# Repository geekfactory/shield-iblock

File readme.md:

# Shield iBlock

Shield para Arduino Uno R3 (y tarjetas que comparten las mismas dimensiones) que permite conectar módulos y accesorios compatibles con el sistema iBlock desarrollado por Geek Factory.

Este shield "exporta" los puertos de la tarjeta Arduino Uno a cables planos de 10 hilos que pueden usarse para interconectar con otros módulos o el protoboard.

El sistema iBlock esta diseñado para usarse durante el aprendizaje de sistemas digitales programables o para desarrollar aplicaciones finales.

## Sistema iBlock

Se trata de una solución de conectividad diseñada para facilitar la reutilización de hardware en prototipos y sistemas realizados para producción. Esta basada en el uso de conectores [IDC (Insulation Displacement Connector)](https://en.wikipedia.org/wiki/Insulation-displacement_connector) y cable plano.

Principalmente se contempla el uso de conectores de 10 pines que permoiten llevar 8 bits o pines de I/O de propósito general y además la tierra y el voltaje de alimentación.

En este sistema cada uno de los módulos se diseñan con una distribución de pines conocida, de forma que sea posible intercambiar y reutilizar el hardware según las necesidades del proyecto.

La distribución de pines en el conector IDC-10 es la siguiente:

1. D0
2. D1
3. D2
4. D3
5. D4
6. D5
7. D6
8. D7
9. GND
10. V+ (3.3 o 5 volts)

Como el arduino Uno dispone de más puertos digitales, se continua en otro conector:

1. D8
2. D9
3. D10
4. D11
5. D12
6. D13
7. NC (sin conexión)
8. NC (sin conexión)
9. GND
10. V+ (3.3 o 5 volts)

La distribución es similar para los pines analógicos de la tarjeta.

## Periféricos y características

* 3 conectores IDC-10 que exponen todos los puertos digitales y analógicos de la tarjeta arduino
	* DIGITAL1 - Expone los pines del 0 al 7 digitales
	* DIGITAL2 - Expone los pines del 8 al 13 digitales
	* ANALOG1 - Expone los pines A0 al A5 analógicos
* 20 conectores tipo servo que brindan acceso a la alimentación y a todas las señales (D0 - D13 y A0 - A5)
* Diseño apilable que permite colocar otros shields o accesorios arriba de esta placa, incluso el conector SPI (ISP) se replica a otros shields
* Se utilizan conectores IDC-10 en angulo que permite la conexión del cable plano cuando hay otro shield colocado encima
* Selección de voltaje de alimentación (3.3 volts o 5 volts) en cada uno de los conectores IDC-10 mediante interruptores
* Conector Nanobus que permite expandir la funcionalidad del shield con otros módulos desarrollados para este estándar
* Dimensiones del PCB: 76.2 mm x 53.34mm (3 x 2.1 pulgadas)

## Contenido del repositorio

1. __root__ - Archivos fuente de EAGLE para esta placa
2. __/documents__ - Documentación adicional, hojas de datos de componentes e instrucciones de ensamble
3. __/production__ - Histórico de gerbers enviados a producción
4. __/extras__ - Dibujos técnicos, imagehes, hardware de montaje adicional y diseños de accesorios relacionados
4. __/firmware__ - Si existe el firmware de prueba o definitivo de esta placa

## Licencia de uso

**Este proyecto se publica como hardware de codigo abierto. Favor de leer detenidamente el archivo license.md para información detallada de la licencia.**

**Reconocimiento-NoComercial-CompartirIgual 4.0 Internacional (CC BY-NC-SA 4.0)**

Esto es un resumen inteligible para humanos (y no un sustituto) de la licencia.

Usted es libre de:

* __Compartir__ — copiar y redistribuir el material en cualquier medio o formato
* __Adaptar__ — remezclar, transformar y crear a partir del material

El licenciador no puede revocar estas libertades mientras cumpla con los términos de la licencia.

Bajo las condiciones siguientes:

* __Reconocimiento__ — Debe reconocer adecuadamente la autoría, proporcionar un enlace a la licencia e indicar si se han realizado cambios. Puede hacerlo de cualquier manera razonable, pero no de una manera que sugiera que tiene el apoyo del licenciador o lo recibe por el uso que hace.

* __NoComercial__ — No puede utilizar el material para una finalidad comercial.

* __CompartirIgual__ — Si remezcla, transforma o crea a partir del material, deberá difundir sus contribuciones bajo la misma licencia que el original.

No hay restricciones adicionales — No puede aplicar términos legales o medidas tecnológicas que legalmente restrinjan realizar aquello que la licencia permite.

## Versiones del Hardware

* 1.0 - Versión inicial

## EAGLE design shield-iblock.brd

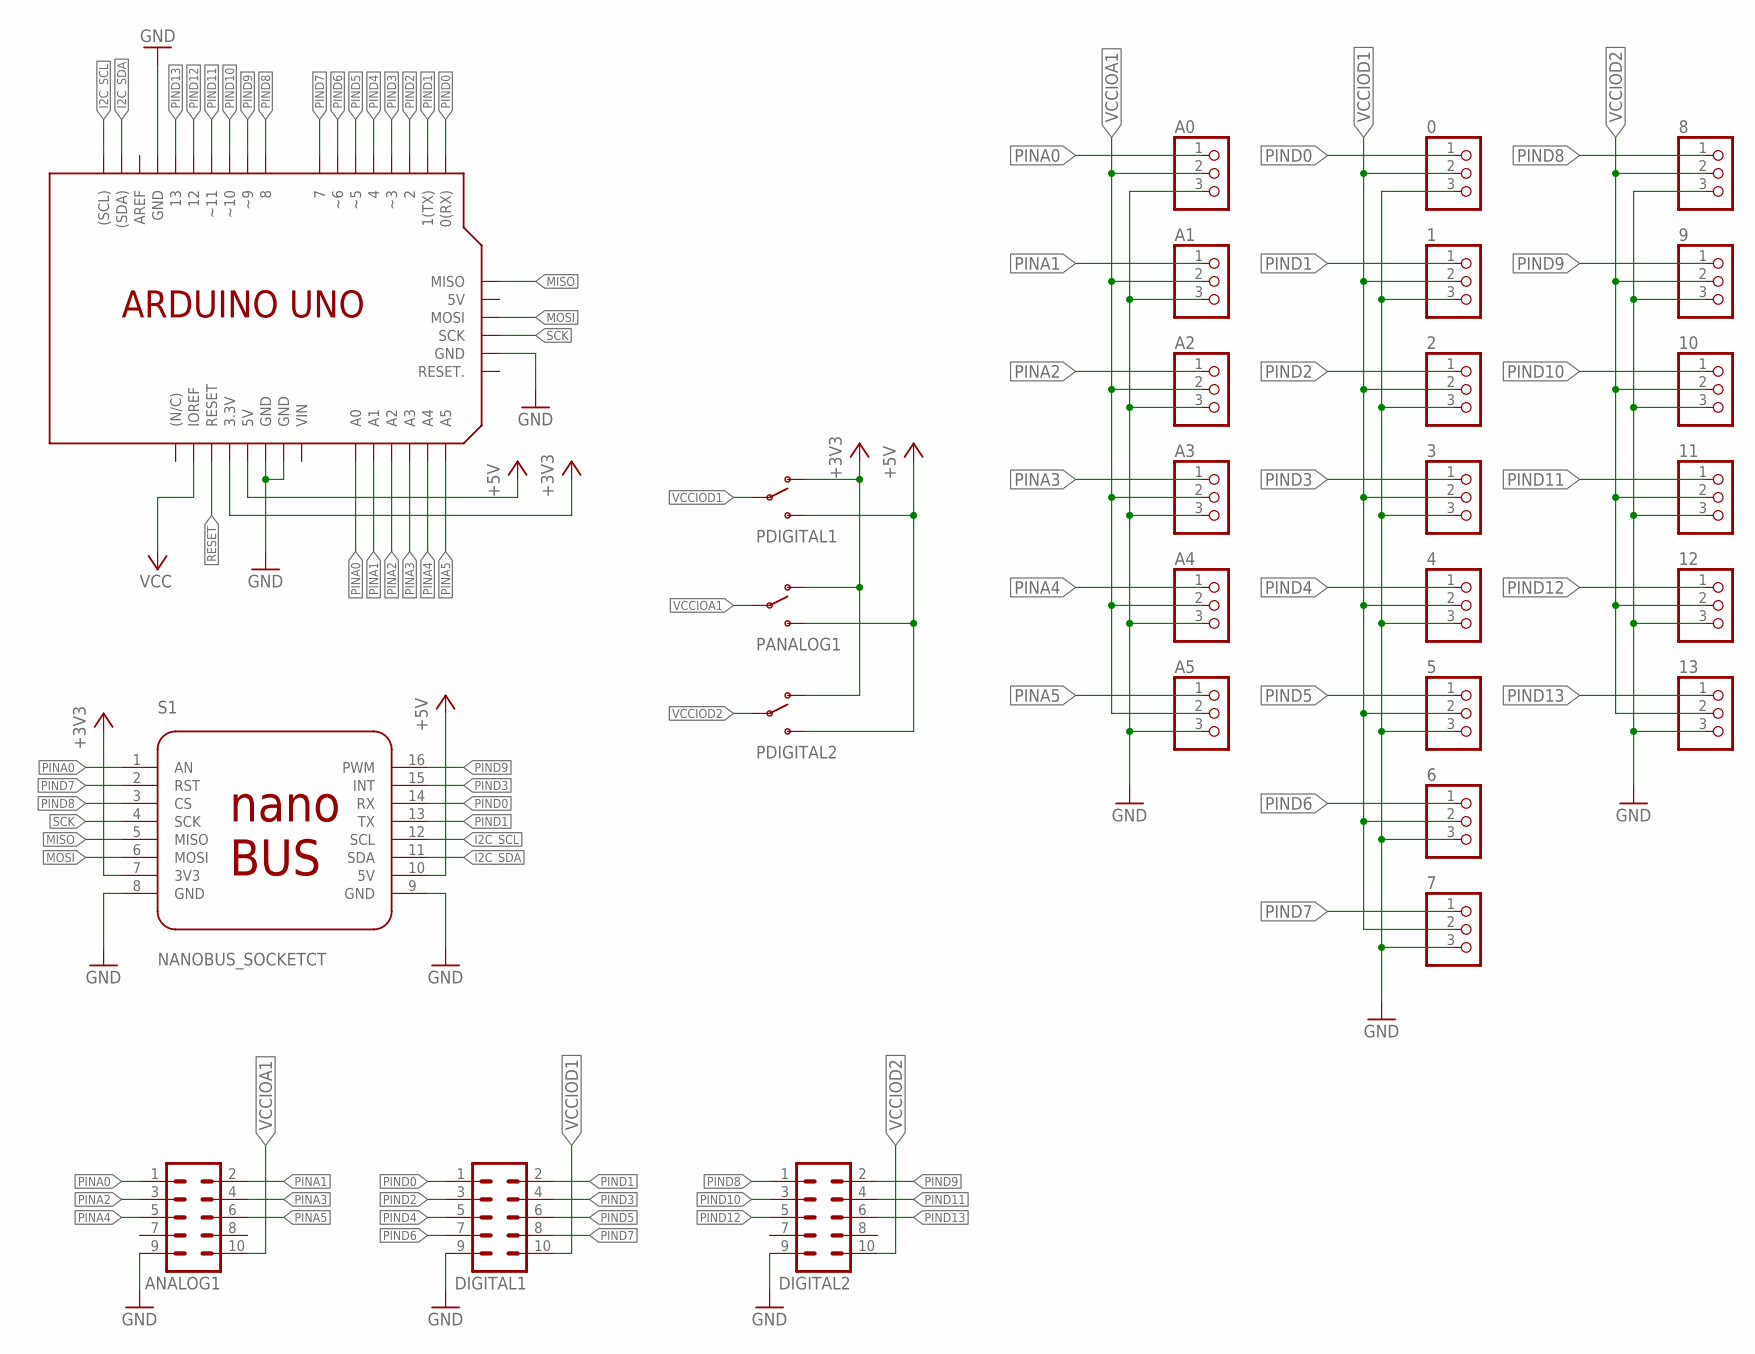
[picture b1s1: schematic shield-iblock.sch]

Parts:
0, 1, 2, 3, 4, 5, 6, 7, 8, 9, 10, 11, 12, 13: PINHD-1X3; 1X03
A0, A1, A2, A3, A4, A5: PINHD-1X3; 1X03
ANALOG1: MA05-2A
ARDUINO1: ARDUINO_UNO_NHNBR; ARDUINO_UNO_NH_NB_ROUND
DIGITAL1, DIGITAL2: MA05-2A
PANALOG1: SWITCH-SPSTPTH; SWITCH-SPDT
PDIGITAL1, PDIGITAL2: SWITCH-SPSTPTH; SWITCH-SPDT
S1: NANOBUS_SOCKETCT; NANOBUS_CONNECTOR_CLEAR_TOP

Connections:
+3V3: ARDUINO1.3V3 (3.3V), PANALOG1.1 (O), PDIGITAL1.1 (O), PDIGITAL2.1 (O), S1.7 (3V3)
+5V: ARDUINO1.5V, PANALOG1.3 (S), PDIGITAL1.3 (S), PDIGITAL2.3 (S), S1.10 (5V)
GND: 0.3, 1.3, 2.3, 3.3, 4.3, 5.3, 6.3, 7.3, 8.3, 9.3, 10.3, 11.3, 12.3, 13.3, A0.3, A1.3, A2.3, A3.3, A4.3, A5.3, ANALOG1.9, ARDUINO1.GND, ARDUINO1.GND. (GND), ARDUINO1.GND.. (GND), ARDUINO1.GND_ (GND), DIGITAL1.9, DIGITAL2.9, S1.8 (GND), S1.9 (GND)
I2C_SCL: ARDUINO1.SCL ((SCL)), S1.12 (SCL)
I2C_SDA: ARDUINO1.SDA ((SDA)), S1.11 (SDA)
MISO: ARDUINO1.MISO, S1.5 (MISO)
MOSI: ARDUINO1.MOSI, S1.6 (MOSI)
PINA0: A0.1, ANALOG1.1, ARDUINO1.A0, S1.1 (AN)
PINA1: A1.1, ANALOG1.2, ARDUINO1.A1
PINA2: A2.1, ANALOG1.3, ARDUINO1.A2
PINA3: A3.1, ANALOG1.4, ARDUINO1.A3
PINA4: A4.1, ANALOG1.5, ARDUINO1.A4
PINA5: A5.1, ANALOG1.6, ARDUINO1.A5
PIND0: 0.1, ARDUINO1.0 (0(RX)), DIGITAL1.1, S1.14 (RX)
PIND1: 1.1, ARDUINO1.1 (1(TX)), DIGITAL1.2, S1.13 (TX)
PIND2: 2.1, ARDUINO1.2, DIGITAL1.3
PIND3: 3.1, ARDUINO1.3 (~3), DIGITAL1.4, S1.15 (INT)
PIND4: 4.1, ARDUINO1.4, DIGITAL1.5
PIND5: 5.1, ARDUINO1.5 (~5), DIGITAL1.6
PIND6: 6.1, ARDUINO1.6 (~6), DIGITAL1.7
PIND7: 7.1, ARDUINO1.7, DIGITAL1.8, S1.2 (RST)
PIND8: 8.1, ARDUINO1.8, DIGITAL2.1, S1.3 (CS)
PIND9: 9.1, ARDUINO1.9 (~9), DIGITAL2.2, S1.16 (PWM)
PIND10: 10.1, ARDUINO1.10 (~10), DIGITAL2.3
PIND11: 11.1, ARDUINO1.11 (~11), DIGITAL2.4
PIND12: 12.1, ARDUINO1.12, DIGITAL2.5
PIND13: 13.1, ARDUINO1.13, DIGITAL2.6
RESET: ARDUINO1.RST (RESET)
SCK: ARDUINO1.SCK, S1.4 (SCK)
VCC: ARDUINO1.IOR (IOREF)
VCCIOA1: A0.2, A1.2, A2.2, A3.2, A4.2, A5.2, ANALOG1.10, PANALOG1.2
VCCIOD1: 0.2, 1.2, 2.2, 3.2, 4.2, 5.2, 6.2, 7.2, DIGITAL1.10, PDIGITAL1.2
VCCIOD2: 8.2, 9.2, 10.2, 11.2, 12.2, 13.2, DIGITAL2.10, PDIGITAL2.2

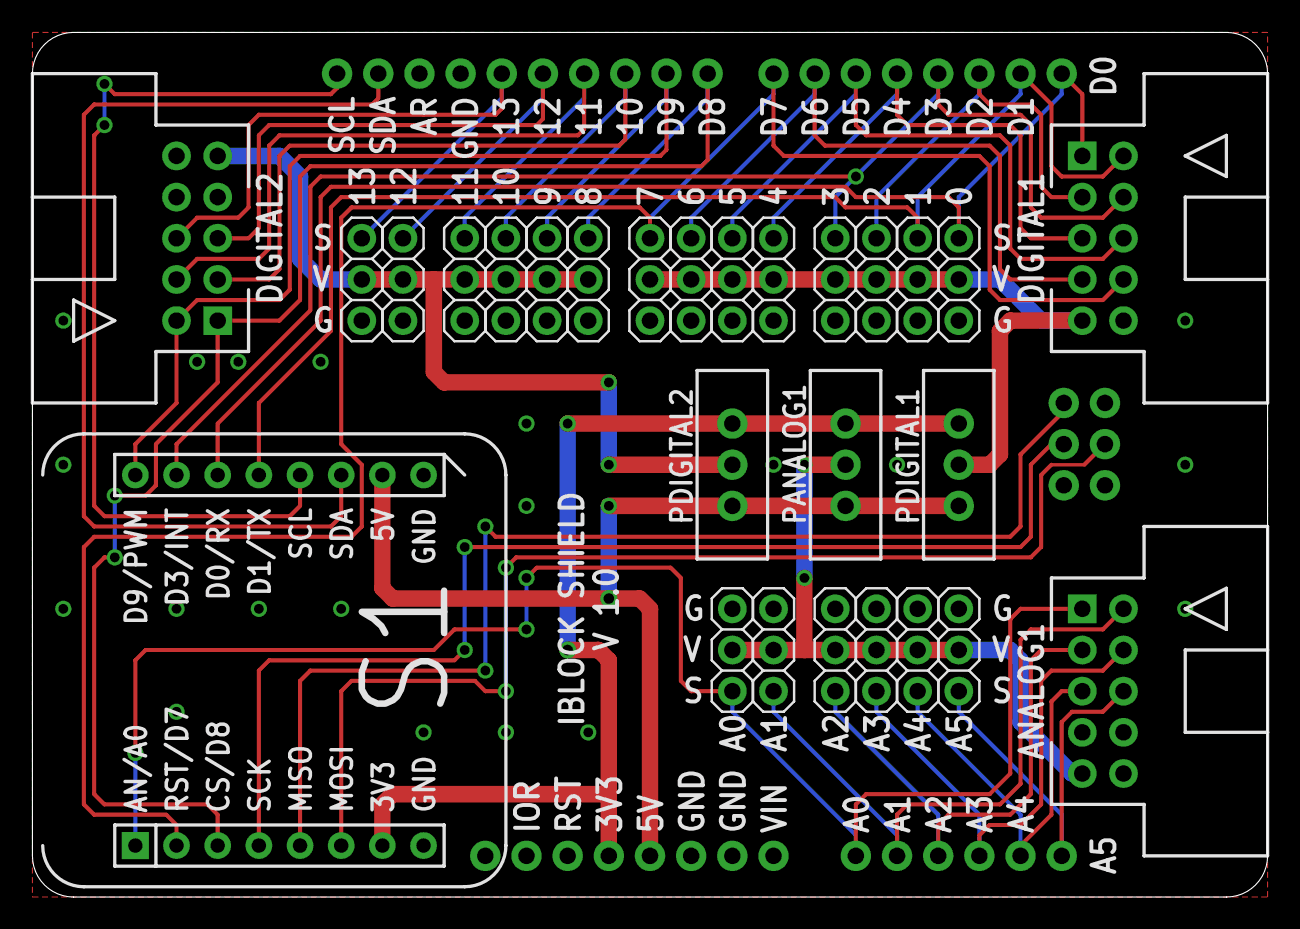
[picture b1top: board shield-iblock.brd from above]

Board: 2 copper layers, 76.2 x 53.3 mm, 28 parts (0 on the bottom side), 31 nets.
